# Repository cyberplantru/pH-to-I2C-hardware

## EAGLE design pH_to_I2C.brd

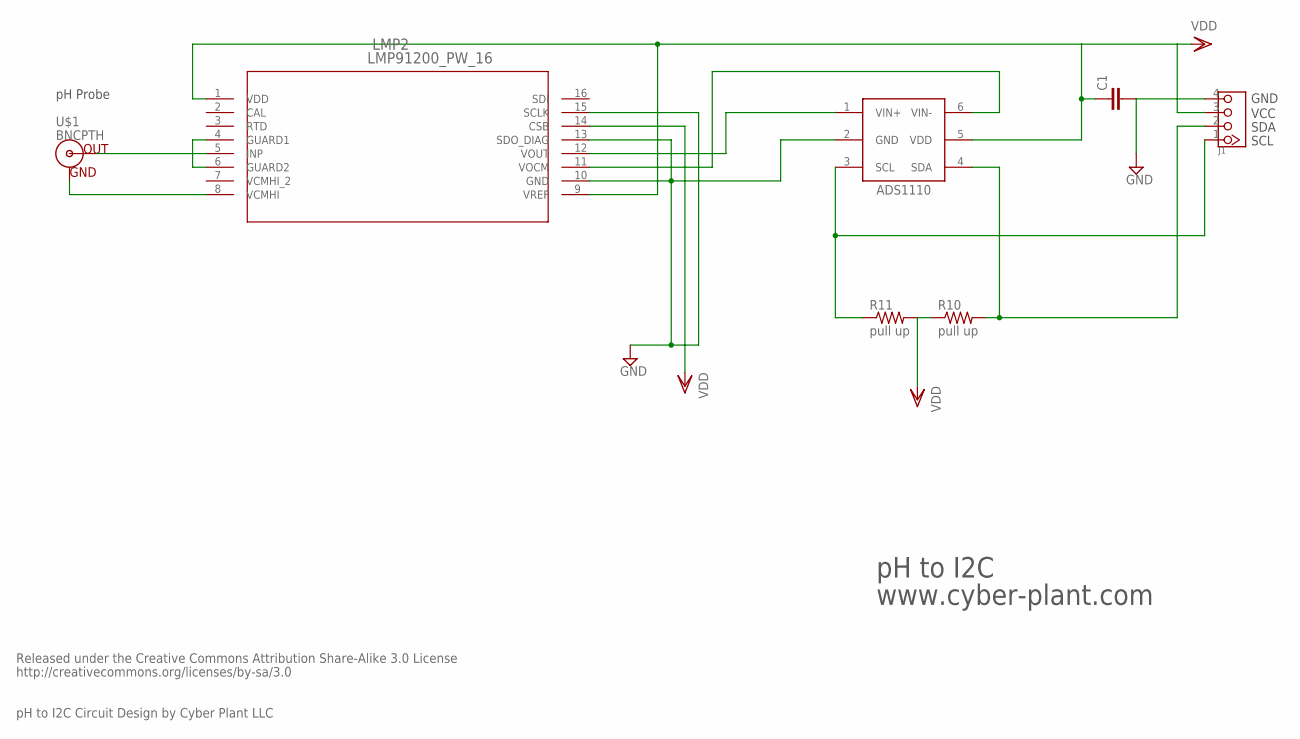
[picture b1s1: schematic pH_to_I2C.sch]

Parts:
C1: CAP1206; 1206
IC1: ADS1110; SOT-23-6
J1: TWIG-4P-2.090D; 4P-2.0-90D
LMP2: LMP91200_PW_16; MTC16
R10, R11: pull up; AXIAL-0.4
U$1: BNCPTH; BNC

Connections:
GND: C1.2, IC1.2 (GND), J1.4, LMP2.10 (GND), LMP2.13 (SDO_DIAG), LMP2.15 (SCLK)
unnamed: IC1.4 (SDA), J1.2, R10.P$2 (2)
unnamed: IC1.1 (VIN+), LMP2.12 (VOUT)
unnamed: IC1.6 (VIN-), LMP2.11 (VOCM)
unnamed: IC1.3 (SCL), J1.1, R11.P$1 (1)
unnamed: LMP2.8 (VCMHI), U$1.GND
unnamed: LMP2.5 (INP), U$1.S (OUT)
unnamed: LMP2.4 (GUARD1), LMP2.6 (GUARD2)
VDD: C1.1, IC1.5 (VDD), J1.3, LMP2.1 (VDD), LMP2.9 (VREF), LMP2.14 (CSB), R10.P$1 (1), R11.P$2 (2)

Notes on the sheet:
pH Probe
GND
VCC
SDA
SCL
pH to I2C
www.cyber-plant.com
Released under the Creative Commons Attribution Share-Alike 3.0 License
http://creativecommons.org/licenses/by-sa/3.0
pH to I2C Circuit Design by Cyber Plant LLC

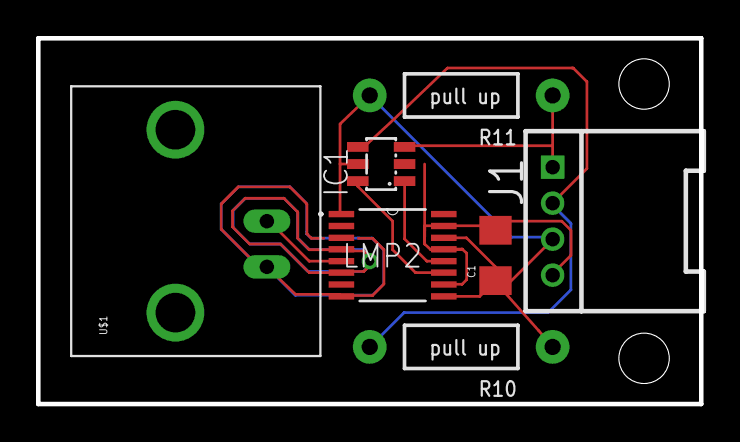
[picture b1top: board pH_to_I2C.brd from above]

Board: 2 copper layers, 36.8 x 20.3 mm, 7 parts (0 on the bottom side), 9 nets.

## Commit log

2014-10-21 master
